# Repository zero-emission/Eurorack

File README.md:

# Eurorack
A collection of open hardware projects for Eurorack

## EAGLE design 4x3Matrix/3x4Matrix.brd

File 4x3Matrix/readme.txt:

A simple 4 in, 3 out Matrix mixer in 10HP.

It's designed to be an easy build as a first SMD project, with 0805 resistors with plenty of space inbetween.

The four inputs can be mixed in a three different ways for three different outputs.

The mixer is DC coupled, so can be used for both CV and audio.

Please double check IC orientation: TL072 pin 1 is down, TL074 pin 1 is up (Skewed side of the IC)
Some examples:

- Mix four cv signals to three different outputs
- Create feedback loops, patching one output back into an input. 
By patching multiple feedback loops you can create complex audio signals and waveshaping. 
Patching effects like delays inbetween can produce infinite feedback.

- For output A turn down input 3 and 4. For output B turn down input 1 and 2. Now you have two independent 2 channel mixers. 
You could use one as a CV attenuator and the other for mixing audio.

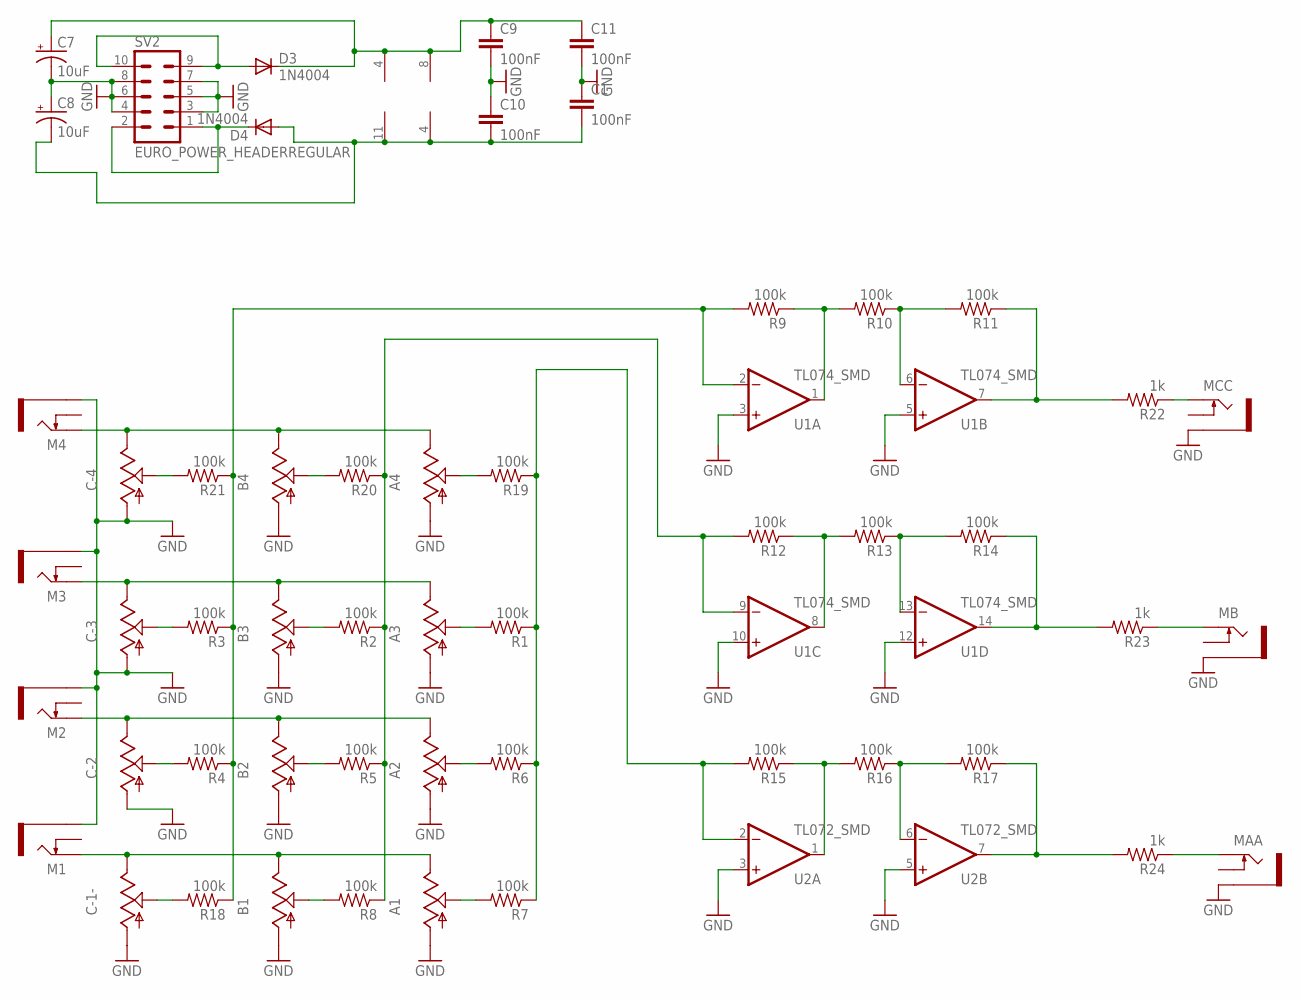
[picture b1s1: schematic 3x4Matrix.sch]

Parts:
A1, A2, A3, A4: 9MM_SNAP-IN_POT_; 9MM_SNAP-IN_POT
B1, B2, B3, B4: 9MM_SNAP-IN_POT_; 9MM_SNAP-IN_POT
C1, C9, C10, C11: 100nF; 0805
C7, C8: 10uF; CPOL-RADIAL-10UF-25V
C-1-, C-2, C-3, C-4: 9MM_SNAP-IN_POT_; 9MM_SNAP-IN_POT
D3, D4: 1N4004; DO41-10
M1, M2, M3, M4: THONKICONNNEW; WQP-PJ301M-12_JACK
MAA: THONKICONNNEW; WQP-PJ301M-12_JACK
MB: THONKICONNNEW; WQP-PJ301M-12_JACK
MCC: THONKICONNNEW; WQP-PJ301M-12_JACK
R1, R2, R3, R4, R5, R6, R7, R8, R9, R10, R11, R12, R13, R14, R15, R16, R17, R18, R19, R20, R21: 100k; 0805
R22, R23, R24: 1k; 0805
SV2: EURO_POWER_HEADERREGULAR; EURO_POWER_HEADER
U1: TL074_SMD; SO14
U2: TL072_SMD; SO08

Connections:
+12UP1: D3.A, SV2.9, SV2.10
-12UP1: D4.C, SV2.1, SV2.2
C-11: R3.1, R4.1, R9.2, R18.1, R21.1, U1.2 (-IN)
GND: A1.1 (A), A2.1 (A), A3.1 (A), A4.1 (A), B1.1 (A), B2.1 (A), B3.1 (A), B4.1 (A), C1.1, C7.2 (-), C8.1 (+), C9.2, C10.1, C11.2, C-1-.1 (A), C-2.1 (A), C-3.1 (A), C-4.1 (A), M1.P$3_SLEEVE (SLEEVE), M2.P$3_SLEEVE (SLEEVE), M3.P$3_SLEEVE (SLEEVE), M4.P$3_SLEEVE (SLEEVE), MAA.P$3_SLEEVE (SLEEVE), MB.P$3_SLEEVE (SLEEVE), MCC.P$3_SLEEVE (SLEEVE), SV2.3, SV2.4, SV2.5, SV2.6, SV2.7, SV2.8, U1.3 (+IN), U1.5 (+IN), U1.10 (+IN), U1.12 (+IN), U2.3 (+IN), U2.5 (+IN)
unnamed: A3.2 (S), R1.2
unnamed: B3.2 (S), R2.2
unnamed: C-3.2 (S), R3.2
unnamed: C-2.2 (S), R4.2
unnamed: B2.2 (S), R5.2
unnamed: A2.2 (S), R6.2
unnamed: B1.2 (S), R8.2
unnamed: C-1-.2 (S), R18.2
unnamed: A1.2 (S), R7.2
unnamed: A4.3 (E), B4.3 (E), C-4.3 (E), M4.P$1_TIP (TIP)
unnamed: MCC.P$1_TIP (TIP), R22.1
unnamed: C1.2, C8.2 (-), C10.2, D4.A, U1.11 (V-), U2.4 (V-)
unnamed: A4.2 (S), R19.2
unnamed: B4.2 (S), R20.2
unnamed: C-4.2 (S), R21.2
unnamed: MB.P$1_TIP (TIP), R23.1
unnamed: MAA.P$1_TIP (TIP), R24.1
unnamed: R1.1, R6.1, R7.1, R15.2, R19.1, U2.2 (-IN)
unnamed: A3.3 (E), B3.3 (E), C-3.3 (E), M3.P$1_TIP (TIP)
unnamed: A2.3 (E), B2.3 (E), C-2.3 (E), M2.P$1_TIP (TIP)
unnamed: A1.3 (E), B1.3 (E), C-1-.3 (E), M1.P$1_TIP (TIP)
unnamed: R12.1, R13.2, U1.8 (OUT)
unnamed: R10.1, R11.2, U1.6 (-IN)
unnamed: R2.1, R5.1, R8.1, R12.2, R20.1, U1.9 (-IN)
unnamed: R11.1, R22.2, U1.7 (OUT)
unnamed: R13.1, R14.2, U1.13 (-IN)
unnamed: R14.1, R23.2, U1.14 (OUT)
unnamed: R16.1, R17.2, U2.6 (-IN)
unnamed: R17.1, R24.2, U2.7 (OUT)
unnamed: C7.1 (+), C9.1, C11.1, D3.C, U1.4 (V+), U2.8 (V+)
PIN1: R9.1, R10.2, U1.1 (OUT)
PINN1: R15.1, R16.2, U2.1 (OUT)

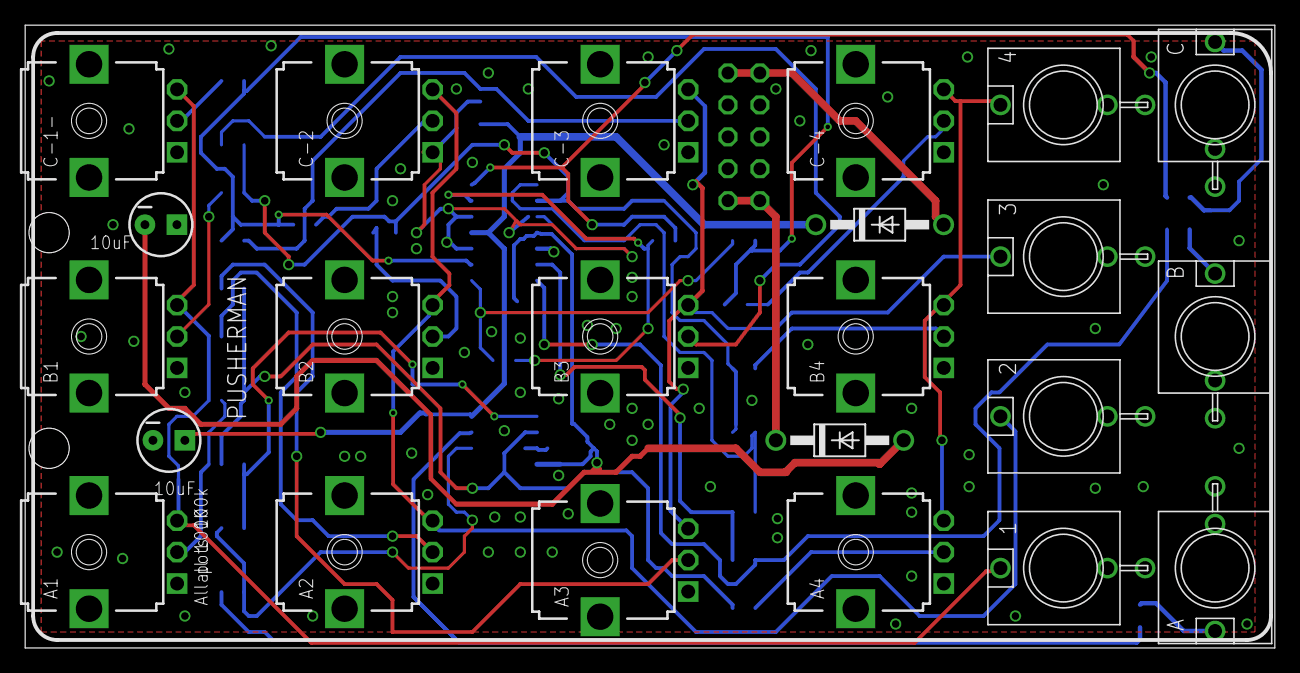
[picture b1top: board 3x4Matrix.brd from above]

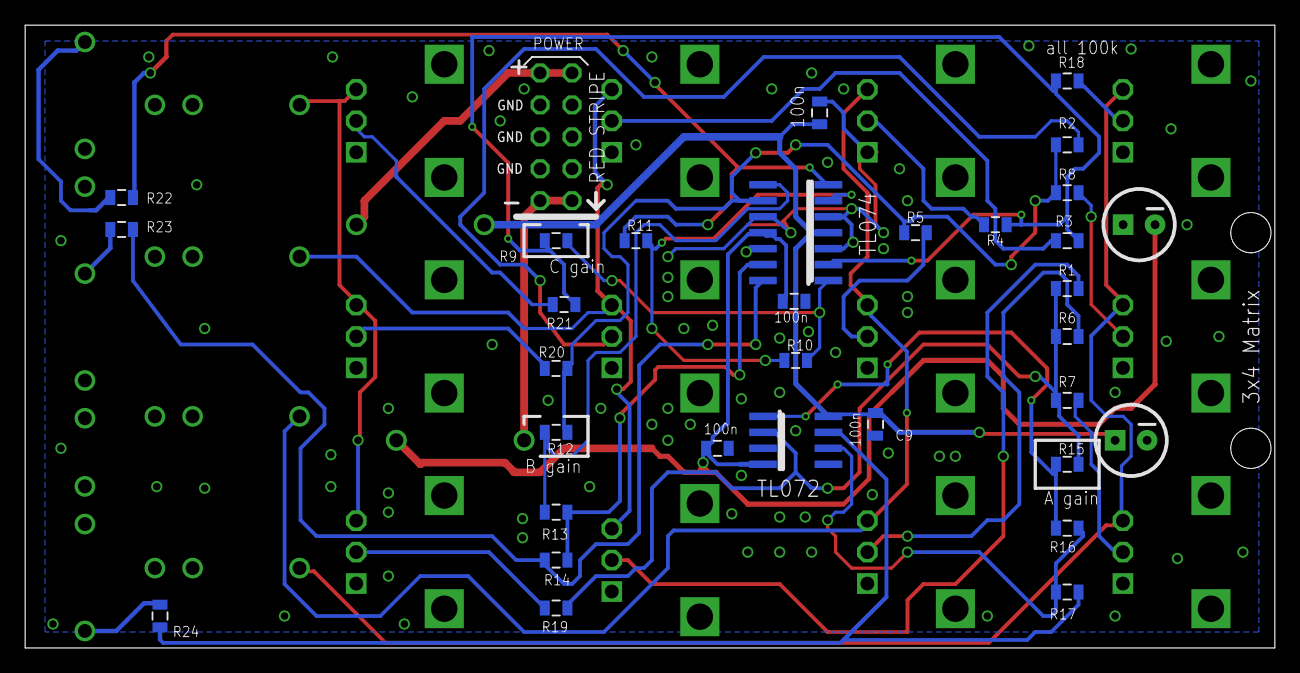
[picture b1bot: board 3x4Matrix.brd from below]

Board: 2 copper layers, 99.4 x 49.5 mm, 54 parts (31 on the bottom side), 36 nets.

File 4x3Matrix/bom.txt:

All resistors 100k except for the three 1k output resistors.

If you like you can change the A B and C gain resistors marked on the pcb to a different value, for higher or lower gain.

Default 100k is unity gain.

_________
BOM

12x 9mm 100K potmeter
7x Thonkiconn jack
1x Power header
Part     Value                    Package              

C1       100nF                    0805                 
C7       10uF                     CPOL-RADIAL-10UF-35V 
C8       10uF                     CPOL-RADIAL-10UF-35V 
C9       100nF                    0805                 
C10      100nF                    0805                 
C11      100nF                    0805                 
D3       1N4004                   DO41-10              
D4       1N4004                   DO41-10              

R1-R21   100k                     0805                 
R22-24   1k                       0805                 
U1       TL074_SMD                SO14     
U2       TL072_SMD                SO08

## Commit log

2017-11-08 Create readme.txt
    Some info about the module
2017-11-08 Create bom.txt
    Part list
2017-11-08 Add files via upload
    The gerber files
2017-11-08 Add files via upload
    Eagle files
2017-11-08 Add files via upload
    A photo of the module
2018-07-27 small note
2020-07-05 Conversion of Eagle files to KiCad current version 5.1.6. Work in progress, critical components already replaced by native KiCad library entities.
2020-07-18 All library parts replaced by default Kicad, new version created which uses 3 TL072 instead of TL072 + TL074 to eliminate crosstalk
2020-07-19 Corrections made to ground planes, trace widths, etc. after visual checks of printout

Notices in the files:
parts and their libraries:
SparkFun-Capacitors: Licensing: Creative Commons ShareAlike 4.0 International - https://creativecommons.org/licenses/by-sa/4.0
